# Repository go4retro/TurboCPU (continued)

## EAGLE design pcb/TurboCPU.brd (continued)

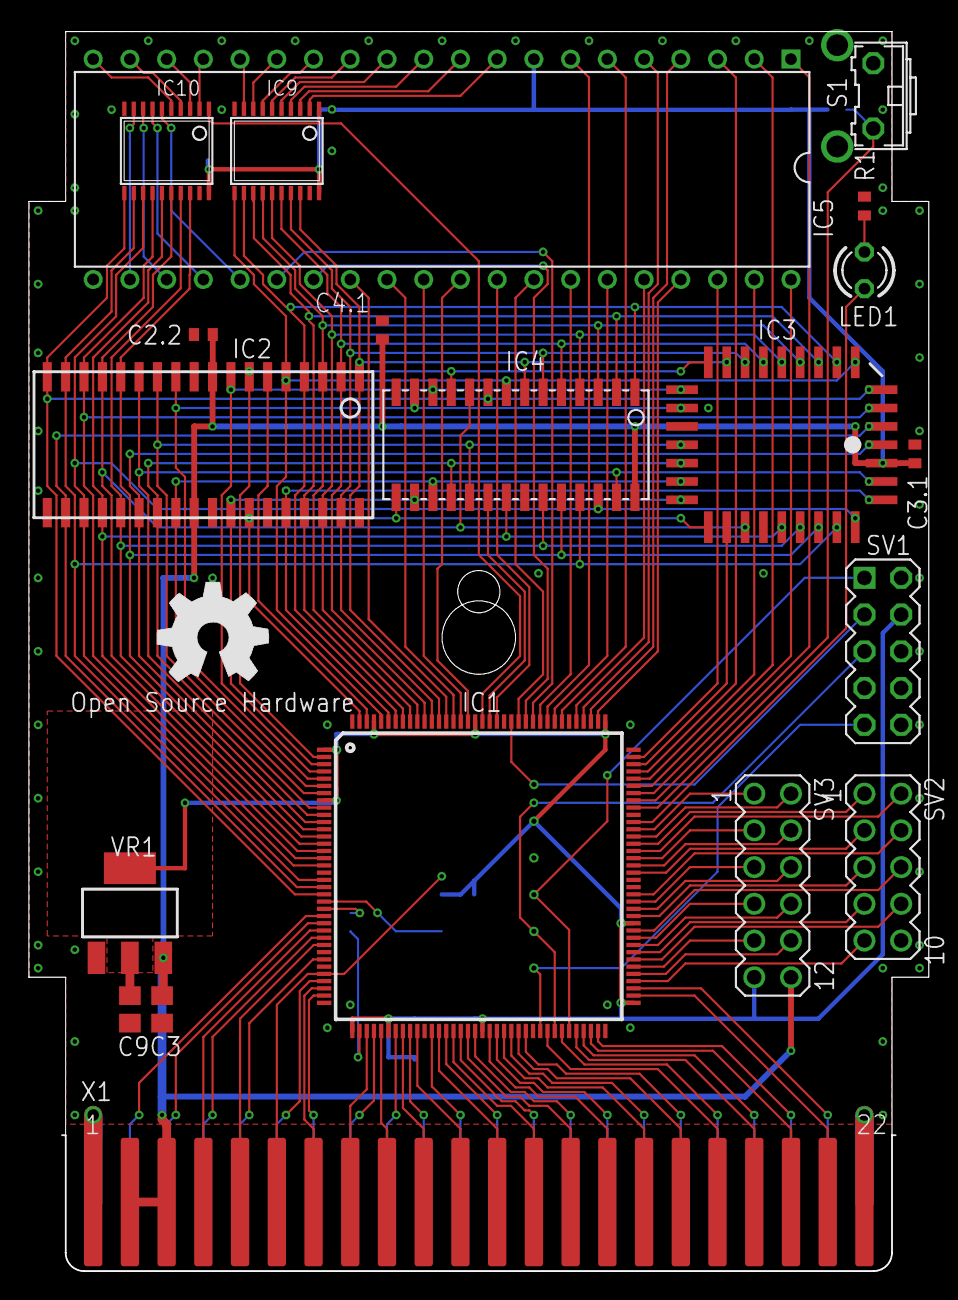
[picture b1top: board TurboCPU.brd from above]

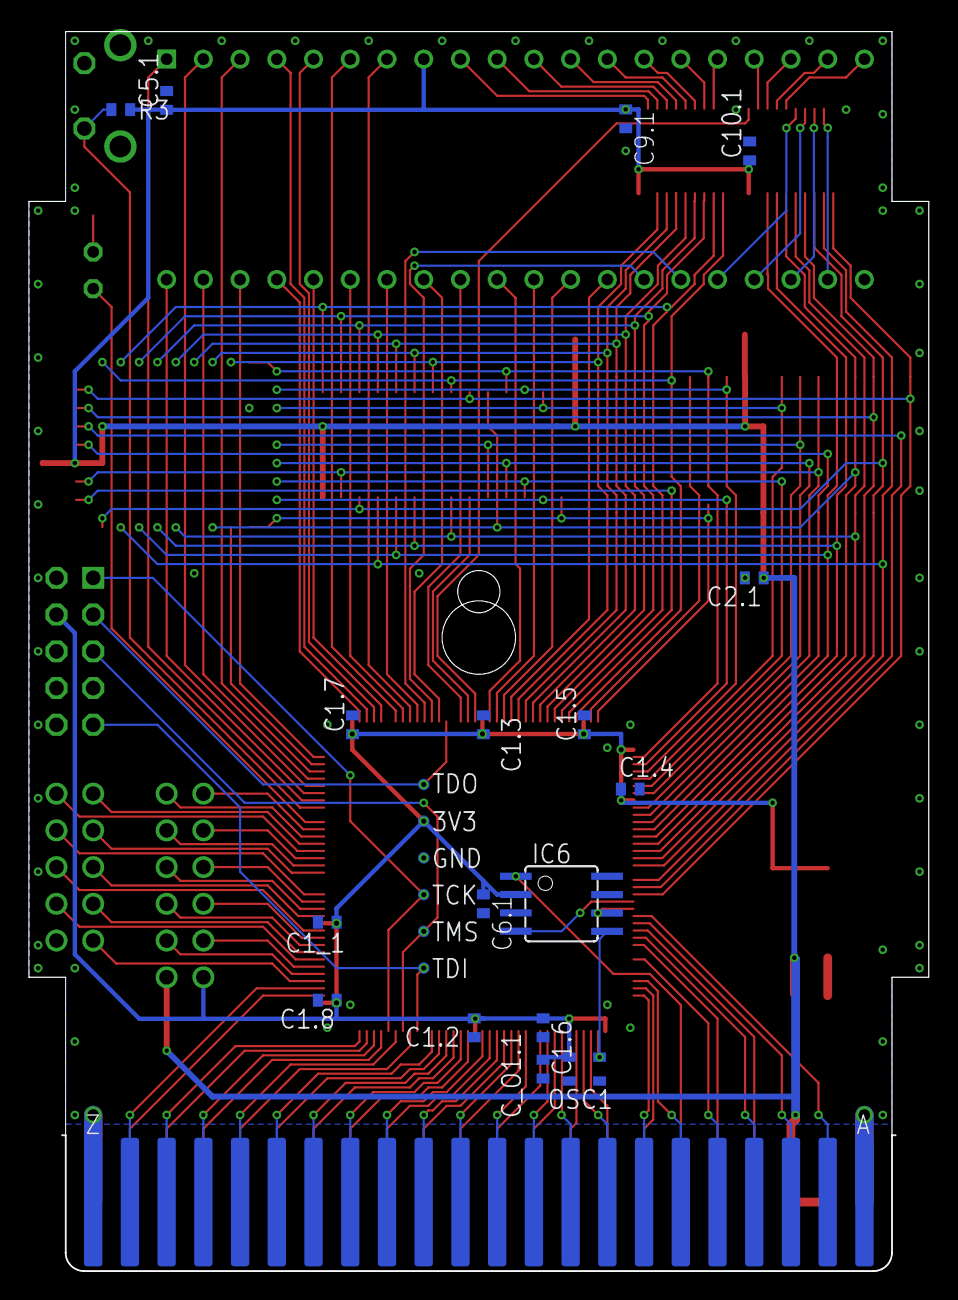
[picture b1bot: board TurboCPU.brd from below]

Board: 2 copper layers, 62.2 x 85.7 mm, 45 parts (23 on the bottom side), 140 nets.

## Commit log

2018-05-21 v1 PCB
2018-05-21 Bare minimum HDL to verify RAM operation
2018-08-22 1MHz 65C816S co-processor working

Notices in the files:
parts and their libraries:
SparkFun: Licensing: CC v3.0 Share-Alike You are welcome to use this library for commercial purposes.
